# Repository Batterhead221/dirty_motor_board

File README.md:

# dirty_motor_board
DRV8461-based stepper motor driver board for Brain_Board, designed for a 17HS4412B NEMA 17 motor with SPI configuration, STEP/DIR control, VM input protection, and chunky motor-output routing.

DRV8461-based stepper motor driver daughter board for Brain_Board.

Dirty_MTR_Board handles the noisy motor-power side of the system: VM input protection, DRV8461 current-regulated stepper drive, motor output routing, and SPI/STEP-DIR control from Brain_Board.

## Overview

This board is designed for a 17HS4412B two-phase stepper motor rated for 3.9 V and 1.2 A/phase. The motor is not powered directly from 3.9 V. Instead, the DRV8461 is supplied from a higher VM rail and regulates coil current internally.

## Key Specs

| Item | Value |
|---|---|
| Driver | TI DRV8461 |
| Motor | 17HS4412B |
| Motor current | 1.2 A/phase |
| VM input | 5-24 V labeled |
| Control | STEP, DIR, EN, nSLEEP, nFAULT |
| Configuration | SPI |
| VM protection | Fuse + SMBJ26A TVS |
| VM bulk cap | 100 µF / 50 V |
| Board role | Motor driver daughter board for Brain_Board |

## Design Notes

- VM is fused and protected with an SMBJ26A TVS diode.
- VM bulk capacitance is provided by a 100 µF / 50 V radial electrolytic capacitor.
- nSLEEP has a 100 kΩ pulldown so the driver defaults to sleep.
- VREF includes a 100 nF capacitor to ground and a DNP 0 Ω option to ground.
- The DRV8461 exposed pad is tied to V-GND with thermal vias.
- Motor output traces are routed wide for 1.2 A/phase operation.

# DIRTY_MOTOR_BOARD

DRV8461-based stepper motor driver daughter board for BRAIN_BOARD, designed around a 17HS4412B NEMA 17 stepper motor with SPI configuration, STEP/DIR control, VM input protection, and high-current motor-output routing.

DIRTY_MOTOR_BOARD handles the noisy motor-power side of the system. It keeps motor current, VM protection, driver switching, and chunky output routing off the main controller board.

## Project Status

In progress / prototype hardware repository.

## System Role

```text
BRAIN_BOARD
    ↓ STEP / DIR / EN / nSLEEP / SPI / nFAULT
DIRTY_MOTOR_BOARD
    ↓ current-regulated phase outputs
17HS4412B NEMA 17 stepper motor
```

BRAIN_BOARD provides logic/control signals. DIRTY_MOTOR_BOARD handles VM power input, DRV8461 motor driving, current regulation, and motor connector routing.

## Key Specs

| Item | Value |
|---|---|
| Driver | TI DRV8461 |
| Motor target | 17HS4412B NEMA 17 stepper |
| Motor current | 1.2 A/phase |
| Motor rated voltage | 3.9 V |
| VM input label | 5-24 V |
| Control style | STEP / DIR |
| Configuration | SPI |
| Logic rail | +3.3V from controller side |
| VM protection | Fuse + SMBJ26A TVS |
| VM bulk capacitor | 100 µF / 50 V |
| Board role | Motor driver daughter board for BRAIN_BOARD |

## Important Motor Note

The 17HS4412B motor is rated for **3.9 V and 1.2 A/phase**, but the board does not simply feed the motor 3.9 V.

The DRV8461 is powered from the VM rail and regulates motor coil current internally. The motor voltage rating is not the same thing as the VM supply voltage for a current-regulated stepper driver.

## Main Features

- DRV8461 stepper motor driver
- STEP/DIR control interface
- SPI configuration interface
- EN, nSLEEP, and nFAULT control/status signals
- VM input fuse/protection path
- SMBJ26A TVS diode on VM
- 100 µF / 50 V VM bulk capacitor
- Wide motor-output routing
- Exposed-pad thermal via strategy
- Motor connector matched to measured coil pairs
- Daughter-board connection to BRAIN_BOARD

## Connectors

### J1 - VM Power Input

| Pin | Signal |
|---:|---|
| 1 | GND |
| 2 | VIN / VM |

J1 brings in the motor power supply rail.

```text
VM input → fuse/protection → VM bulk capacitance → DRV8461 VM
```

### J2 - Motor Control

| Pin | Signal |
|---:|---|
| 1 | GND |
| 2 | +3V3 |
| 3 | EN |
| 4 | nSLEEP |
| 5 | nFAULT |
| 6 | STEP |
| 7 | DIR |
| 8 | DRV_CS |

J2 carries the main logic/control signals between BRAIN_BOARD and DIRTY_MOTOR_BOARD.

### J3 - SPI

| Pin | Signal |
|---:|---|
| 1 | GND |
| 2 | +3V3 |
| 3 | SPI_MISO |
| 4 | SPI_MOSI |
| 5 | SPI_SCK |
| 6 | GND |

J3 carries the SPI bus used for DRV8461 configuration/status access.

### M1 - Motor Output

| Pin | Signal |
|---:|---|
| 1 | AOUT2 |
| 2 | BOUT1 |
| 3 | BOUT2 |
| 4 | AOUT1 |

Measured motor coil pairs:

| Coil | Motor connector pins |
|---|---|
| Coil A | pins 1 and 4 |
| Coil B | pins 2 and 3 |

## DRV8461 Control Signals

| Signal | Direction | Purpose |
|---|---|---|
| STEP | Controller → driver | Step pulse input |
| DIR | Controller → driver | Direction input |
| EN | Controller → driver | Driver enable control |
| nSLEEP | Controller → driver | Sleep/wake control |
| nFAULT | Driver → controller | Fault/status output |
| DRV_CS | Controller → driver | SPI chip select |
| SPI_MISO | Driver → controller | SPI data back to controller |
| SPI_MOSI | Controller → driver | SPI data to driver |
| SPI_SCK | Controller → driver | SPI clock |

## Power Architecture

```text
VM input
    ↓
fuse/protection
    ↓
SMBJ26A TVS clamp to GND
    ↓
100 µF / 50 V bulk capacitor
    ↓
DRV8461 VM pins
    ↓
AOUT/BOUT motor phase outputs
```

Logic power comes from the controller side:

```text
BRAIN_BOARD +3.3V → DIRTY_MOTOR_BOARD logic/interface rail
```

## Design Notes

- VM is fused and protected with an SMBJ26A TVS diode.
- VM bulk capacitance is provided by a 100 µF / 50 V radial electrolytic capacitor.
- nSLEEP has a 100 kΩ pulldown so the driver defaults to sleep.
- VREF includes a 100 nF capacitor to ground and a DNP 0 Ω option to ground.
- The DRV8461 exposed pad is tied to V-GND with thermal vias.
- Motor output traces are routed wide for 1.2 A/phase operation.
- Keep motor-output routing away from sensitive logic/control traces where practical.
- Keep VM bulk capacitance close to the driver power path.
- The board is intentionally separated from BRAIN_BOARD to keep noisy motor current off the main controller PCB.

## Bring-Up Checklist

1. Inspect DRV8461 soldering, exposed pad, and thermal vias.
2. Check for shorts between VM and GND before applying power.
3. Check for shorts between +3.3V and GND.
4. Power logic side first if possible and confirm +3.3V.
5. Confirm nSLEEP default behavior before enabling the driver.
6. Apply VM current-limited during first power-up.
7. Confirm SPI communication with the DRV8461.
8. Confirm nFAULT is not asserted.
9. Connect motor and verify coil-pair order.
10. Start with low current/settings before full 1.2 A/phase operation.

## Repository Output Images

Expected image paths for GitHub README rendering:

```text
Outputs/
  IMG/
    3D-T.png
    3D-B.png
    SCHEMATIC.png
    L1-SIG.png
    L2-3V3.png
    L3-GND.png
    L4-MIX.png
```

## Safety / Design Note

DIRTY_MOTOR_BOARD handles higher-current motor power. Verify VM polarity, current limit, motor wiring, driver configuration, thermal behavior, and fuse/protection choices before running a motor under load.

Designed & engineered by Brandon Shelly.

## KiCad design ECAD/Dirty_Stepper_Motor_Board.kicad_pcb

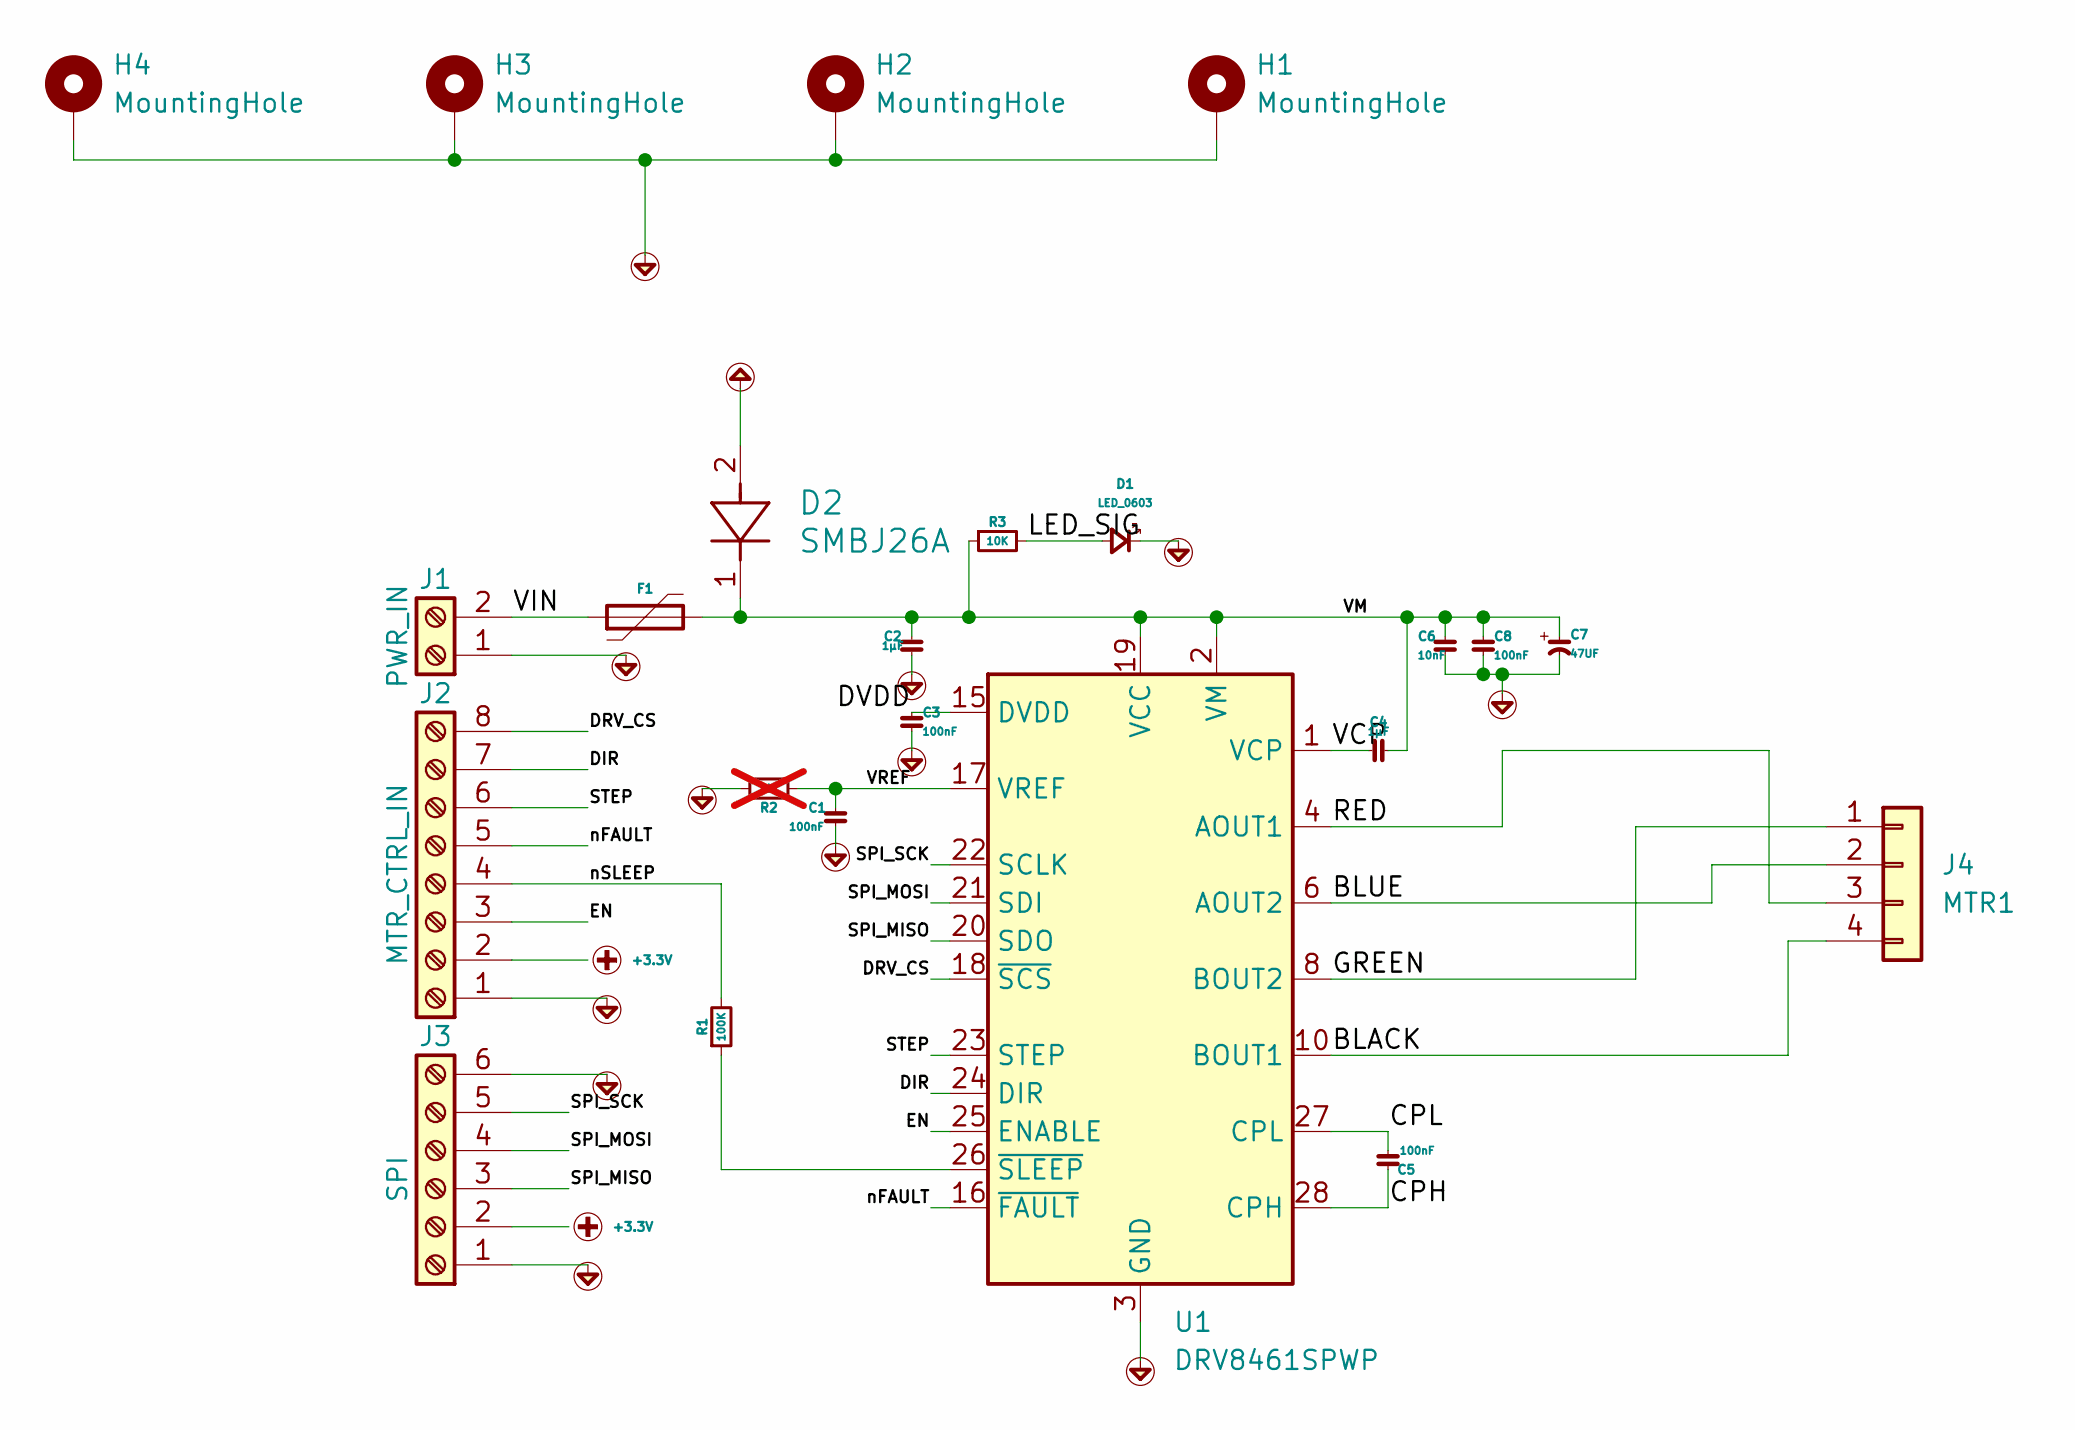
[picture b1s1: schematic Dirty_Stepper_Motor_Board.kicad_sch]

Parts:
C1, C3, C5, C8: 100nF; C_0603_1608Metric
C2, C4: 1µF; C_0805_2012Metric; MPN C3216X5R1V226M160AC
C6: 10nF; C_0603_1608Metric
C7: 47UF; PCAP_8x11_5-THRU-ELECT_NCA
D1: LED_0603; LED_0603_1608Metric
D2: SMBJ26A; SMBJSeries_LTF
F1: Polyfuse; Fuse_1206_3216Metric
H1, H2, H3, H4: MountingHole; MountingHole_3.2mm_M3_ISO14580_Pad
J1: PWR_IN; TE_3-641126-2
J2: MTR_CTRL_IN; JST_EH_B8B-EH-A_1x08_P2.50mm_Vertical
J3: SPI; JST_EH_B6B-EH-A_1x06_P2.50mm_Vertical
J4: MTR1; MTA-4
R1: 100K; R_0603_1608Metric
R2: 0; R_0603_1608Metric; not fitted
R3: 10K; R_0603_1608Metric
U1: DRV8461SPWP; Texas_PWP0028V_TSSOP-28-1EP_4.4x9.7mm_P0.65mm_EP3.4x9.7mm_M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

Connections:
+3.3V: J2.2, J3.2
/BLACK: J4.4, U1.10 (BOUT1), U1.11 (BOUT1)
/BLUE: J4.2, U1.6 (AOUT2), U1.7 (AOUT2)
/CPH: C5.2, U1.28 (CPH)
/CPL: C5.1, U1.27 (CPL)
/DIR: J2.7, U1.24 (DIR)
/DRV_CS: J2.8, U1.18 (~SCS)
/DVDD: C3.2, U1.15 (DVDD)
/EN: J2.3, U1.25 (ENABLE)
/GREEN: J4.1, U1.8 (BOUT2), U1.9 (BOUT2)
/LED_SIG: D1.2 (A), R3.2
/RED: J4.3, U1.4 (AOUT1), U1.5 (AOUT1)
/SPI_MISO: J3.3, U1.20 (SDO)
/SPI_MOSI: J3.4, U1.21 (SDI)
/SPI_SCK: J3.5, U1.22 (SCLK)
/STEP: J2.6, U1.23 (STEP)
/VCP: C4.1, U1.1 (VCP)
/VIN: F1.1, J1.2
/VM: C2.2, C4.2, C6.2, C7.1, C8.2, D2.1, F1.2, R3.1, U1.2 (VM), U1.13 (VM), U1.19 (VCC)
/VREF: C1.2, R2.1, U1.17 (VREF)
/nFAULT: J2.5, U1.16 (~FAULT)
/nSLEEP: J2.4, R1.2
unnamed: R1.1, U1.26 (~SLEEP)
V-GND: C1.1, C2.1, C3.1, C6.1, C7.2, C8.1, D1.1 (K), D2.2, H1.1 (1_1), H2.1 (1_1), H3.1 (1_1), H4.1 (1_1), J1.1, J2.1, J3.1, J3.6, R2.2, U1.3 (GND), U1.12 (GND), U1.14 (GND), U1.29 (GND)

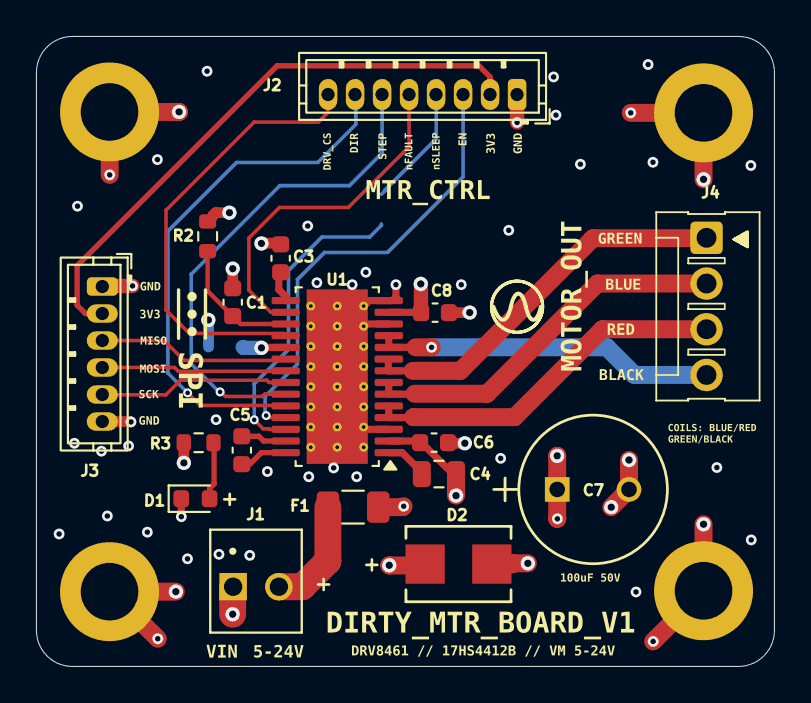
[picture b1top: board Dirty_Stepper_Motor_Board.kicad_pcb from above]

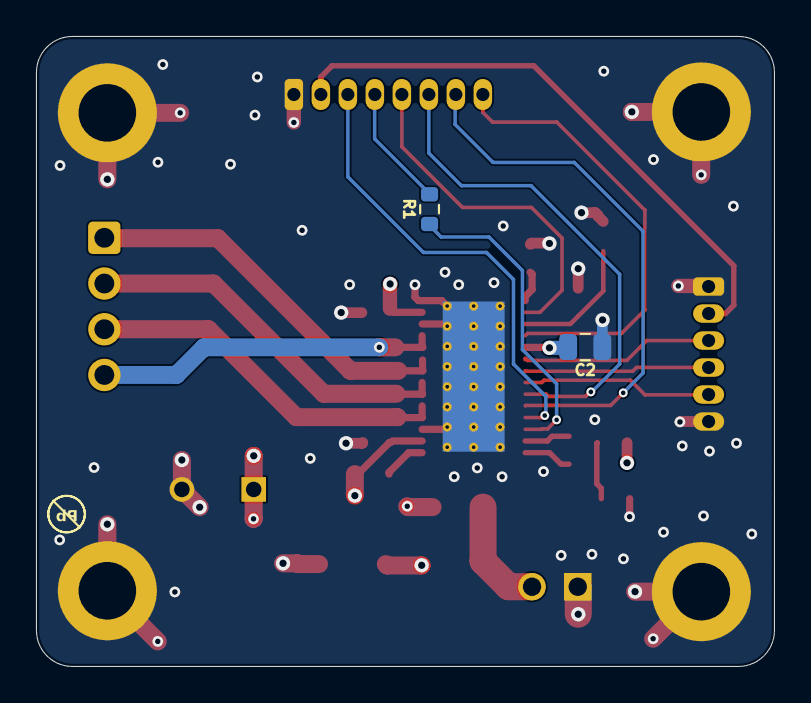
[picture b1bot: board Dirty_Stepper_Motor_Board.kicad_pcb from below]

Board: 4 copper layers, 41.0 x 35.0 mm, 23 parts (2 on the bottom side), 24 nets.

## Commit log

2026-05-03 folder restructure
2026-05-13 Revised repo
2026-05-13 Added stitching vias
2026-05-24 repo update
2026-05-24 cont.
